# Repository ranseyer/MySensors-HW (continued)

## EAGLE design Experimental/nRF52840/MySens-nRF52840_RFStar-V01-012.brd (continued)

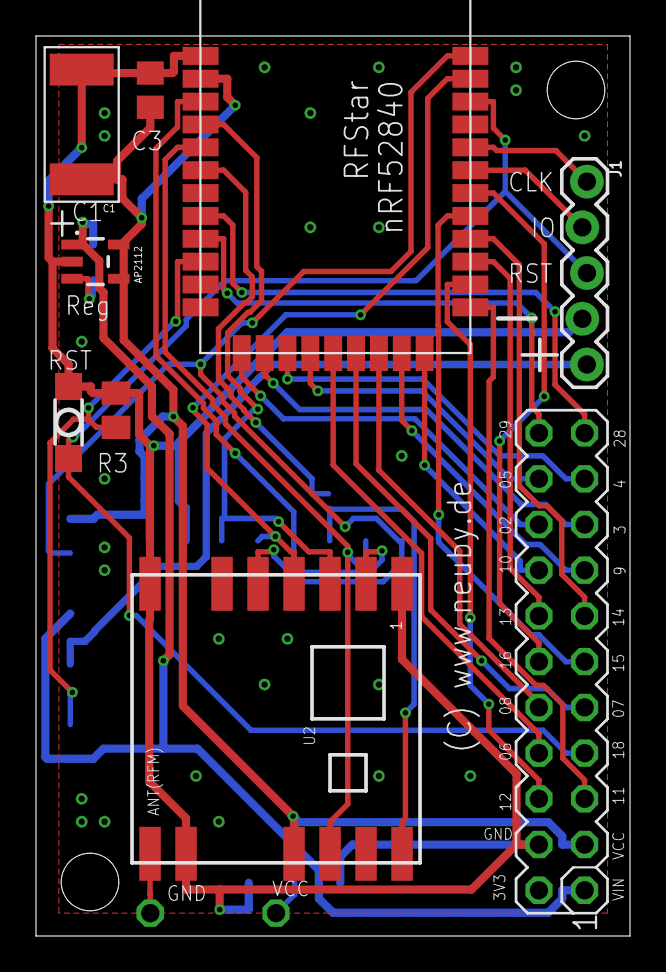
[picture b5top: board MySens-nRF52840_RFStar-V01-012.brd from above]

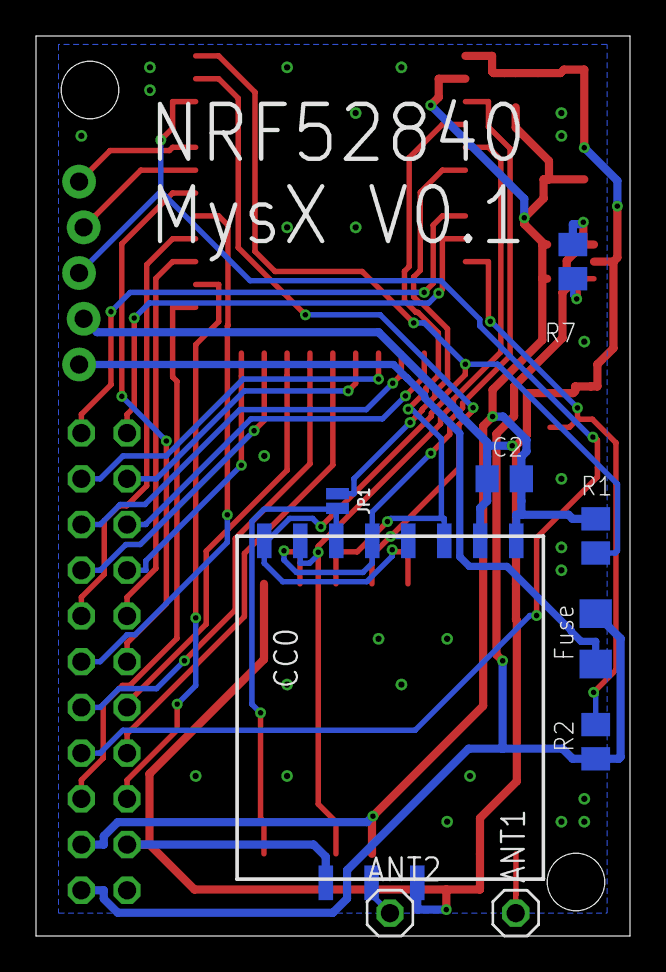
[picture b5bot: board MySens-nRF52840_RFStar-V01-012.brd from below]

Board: 2 copper layers, 33.0 x 50.0 mm, 18 parts (9 on the bottom side), 35 nets.

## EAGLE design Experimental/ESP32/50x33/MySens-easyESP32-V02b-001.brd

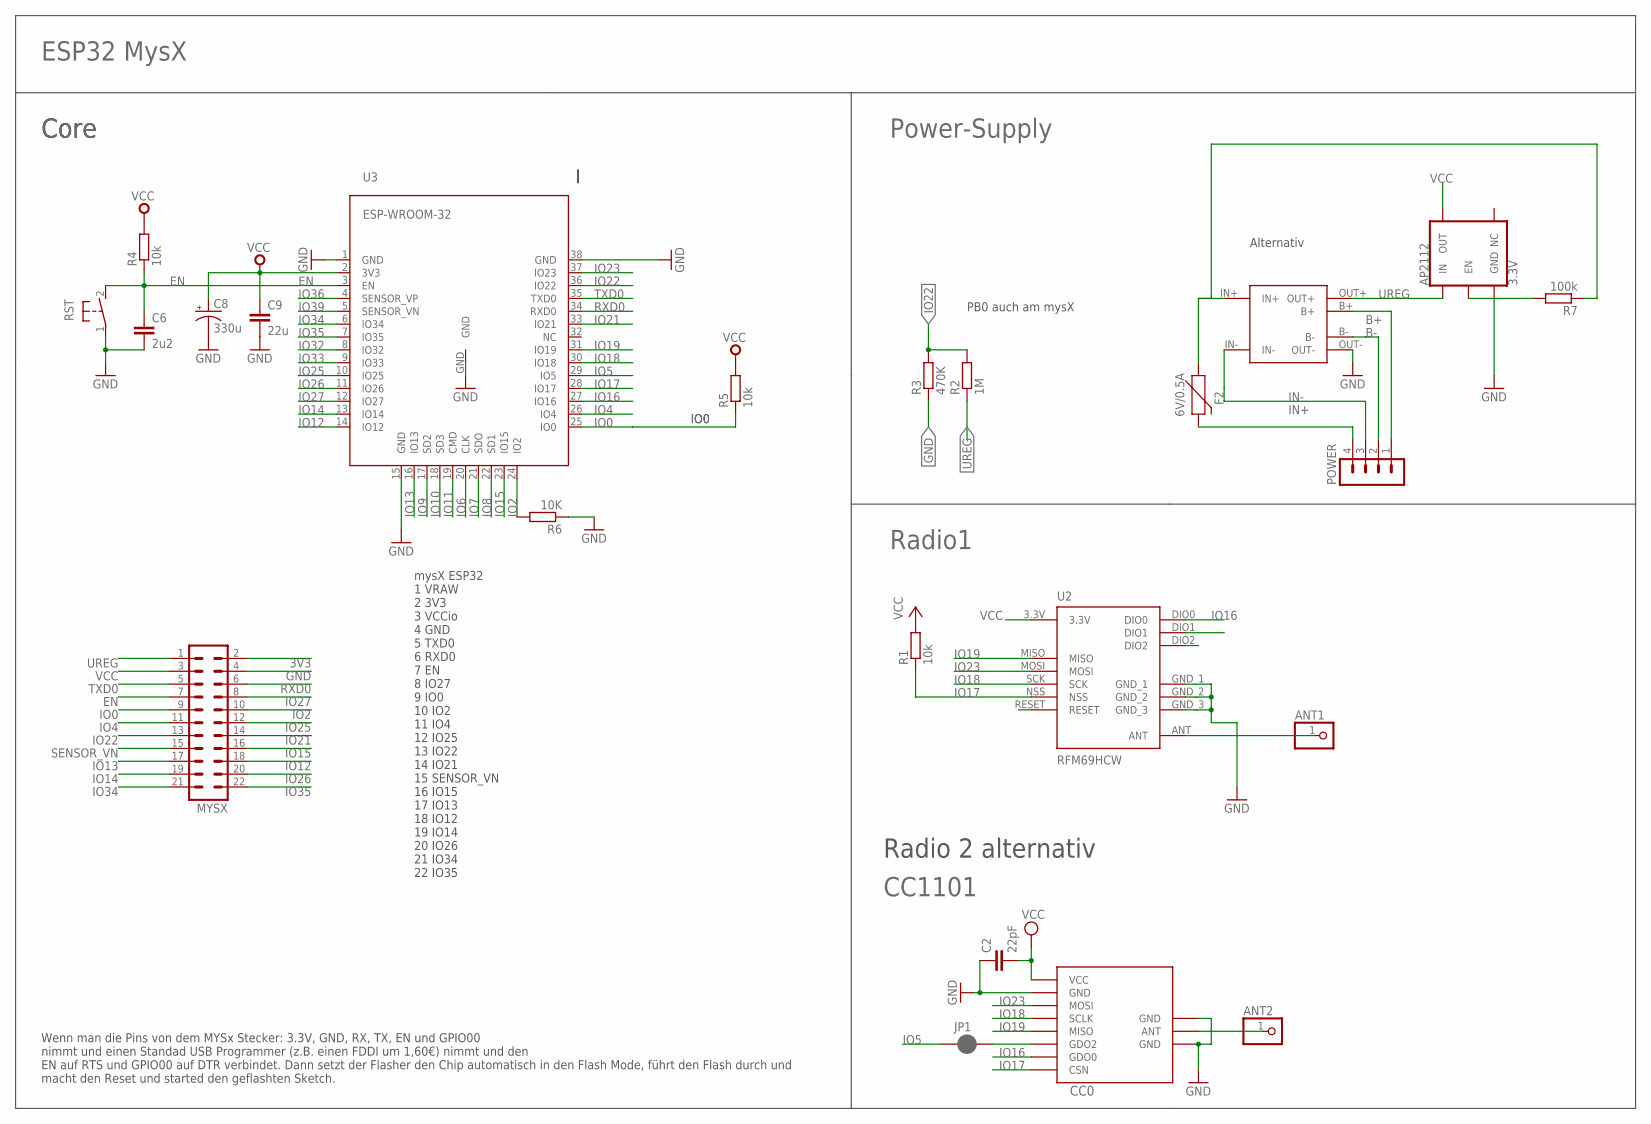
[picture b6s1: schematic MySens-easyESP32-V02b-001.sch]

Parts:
ANT1, ANT2: PINHD-1X1; 1X01
AP2112: 3.3V; SOT23-5
C2: 22pF; C0805
C6: 2u2; C0805
C8: 330u; VISHAY_C
C9: 22u; C0805
CC0: CC1101; CC1101_MODULE1_SMD
F2: 6V/0.5A; 1206
JP1: JUMPER-SMT_2_NC_PASTE_NO-SILK; SMT-JUMPER_2_NC_PASTE_NO-SILK
MYSX: MA11-2
POWER: MA04-1
R1, R4: 10k; M0805
R2: 1M; M0805
R3: 470K; M0805
R5: 10k; R0603
R6: 10K; M0805
R7: 100k; M0805
RST: DTSM-3
TP4056: TP4056-MODULE; TP4056-LITHIUM-PROTECTED-MODULE
U2: RFM69HCW; RFM69HCW-XXXS2
U3: ESP-WROOM-32

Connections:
3V3: MYSX.2
ANT0: ANT2.1, CC0.ANT
ANT1: ANT1.1, U2.ANT
B+: POWER.1, TP4056.B+
B-: POWER.2, TP4056.B-
EN: C6.1, MYSX.7, R4.1, RST.2, U3.3 (EN)
GND: AP2112.2 (GND), C2.1, C6.2, C8.-, C9.2, CC0.GND@0 (GND), CC0.GND@1 (GND), CC0.GND@2 (GND), MYSX.4, R3.1, R6.1, RST.1, TP4056.OUT-, U2.GND_1, U2.GND_2, U2.GND_3, U3.1 (GND), U3.15 (GND), U3.38 (GND), U3.GND
IN+: F2.2, POWER.4
IN++: F2.1, R7.1, TP4056.IN+
IN-: POWER.3, TP4056.IN-
IO0: MYSX.9, R5.1, U3.25 (IO0)
IO2: MYSX.10, R6.2, U3.24 (IO2)
IO4: MYSX.11, U3.26 (IO4)
IO5: JP1.1, U3.29 (IO5)
IO6: U3.20 (CLK)
IO7: U3.21 (SDO)
IO8: U3.22 (SD1)
IO9: U3.17 (SD2)
IO10: U3.18 (SD3)
IO11: U3.19 (CMD)
IO12: MYSX.18, U3.14 (IO12)
IO13: MYSX.17, U3.16 (IO13)
IO14: MYSX.19, U3.13 (IO14)
IO15: MYSX.16, U3.23 (IO15)
IO16: CC0.GDO0, U2.DIO0, U3.27 (IO16)
IO17: CC0.CSN, R1.1, U2.NSS, U3.28 (IO17)
IO18: CC0.SCLK, U2.SCK, U3.30 (IO18)
IO19: CC0.MISO, U2.MISO, U3.31 (IO19)
IO21: MYSX.14, U3.33 (IO21)
IO22: MYSX.13, R2.2, R3.2, U3.36 (IO22)
IO23: CC0.MOSI, U2.MOSI, U3.37 (IO23)
IO25: MYSX.12, U3.10 (IO25)
IO26: MYSX.20, U3.11 (IO26)
IO27: MYSX.8, U3.12 (IO27)
IO32: U3.8 (IO32)
IO33: U3.9 (IO33)
IO34: MYSX.21, U3.6 (IO34)
IO35: MYSX.22, U3.7 (IO35)
IO36: U3.4 (SENSOR_VP)
IO39: U3.5 (SENSOR_VN)
MAYBE_IO5: CC0.GDO2, JP1.2
unnamed: AP2112.3 (EN), R7.2
RXD0: MYSX.6, U3.34 (RXD0)
SENSOR_VN: MYSX.15
TXD0: MYSX.5, U3.35 (TXD0)
UREG: AP2112.1 (IN), MYSX.1, R2.1, TP4056.OUT+
VCC: AP2112.5 (OUT), C2.2, C8.+, C9.1, CC0.VCC, MYSX.3, R1.2, R4.2, R5.2, U2.3.3V, U3.2 (3V3)

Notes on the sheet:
mysX ESP32 1 VRAW 2 3V3 3 VCCio 4 GND 5 TXD0 6 RXD0 7 EN 8 IO27 9 IO0 10 IO2 11 IO4 12 IO25 13 IO22 14 IO21 15 SENSOR_VN 16 IO15 17 IO13 18 IO12 19 IO14 20 IO26 21 IO34 22 IO35
PB0 auch am mysX
Radio1
ESP32 MysX
Radio 2 alternativ
CC1101
Wenn man die Pins von dem MYSx Stecker: 3.3V, GND, RX, TX, EN und GPIO00 nimmt und einen Standad USB Programmer (z.B. einen FDDI um 1,60€) nimmt und den EN auf RTS und GPIO00 auf DTR verbindet. Dann setzt der Flasher den Chip automatisch in den Flash Mode, führt den Flash durch und macht den Reset 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
Alternativ
Core
Power-Supply

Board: 2 copper layers, 23 parts (11 on the bottom side), 35 nets, no tracks yet.

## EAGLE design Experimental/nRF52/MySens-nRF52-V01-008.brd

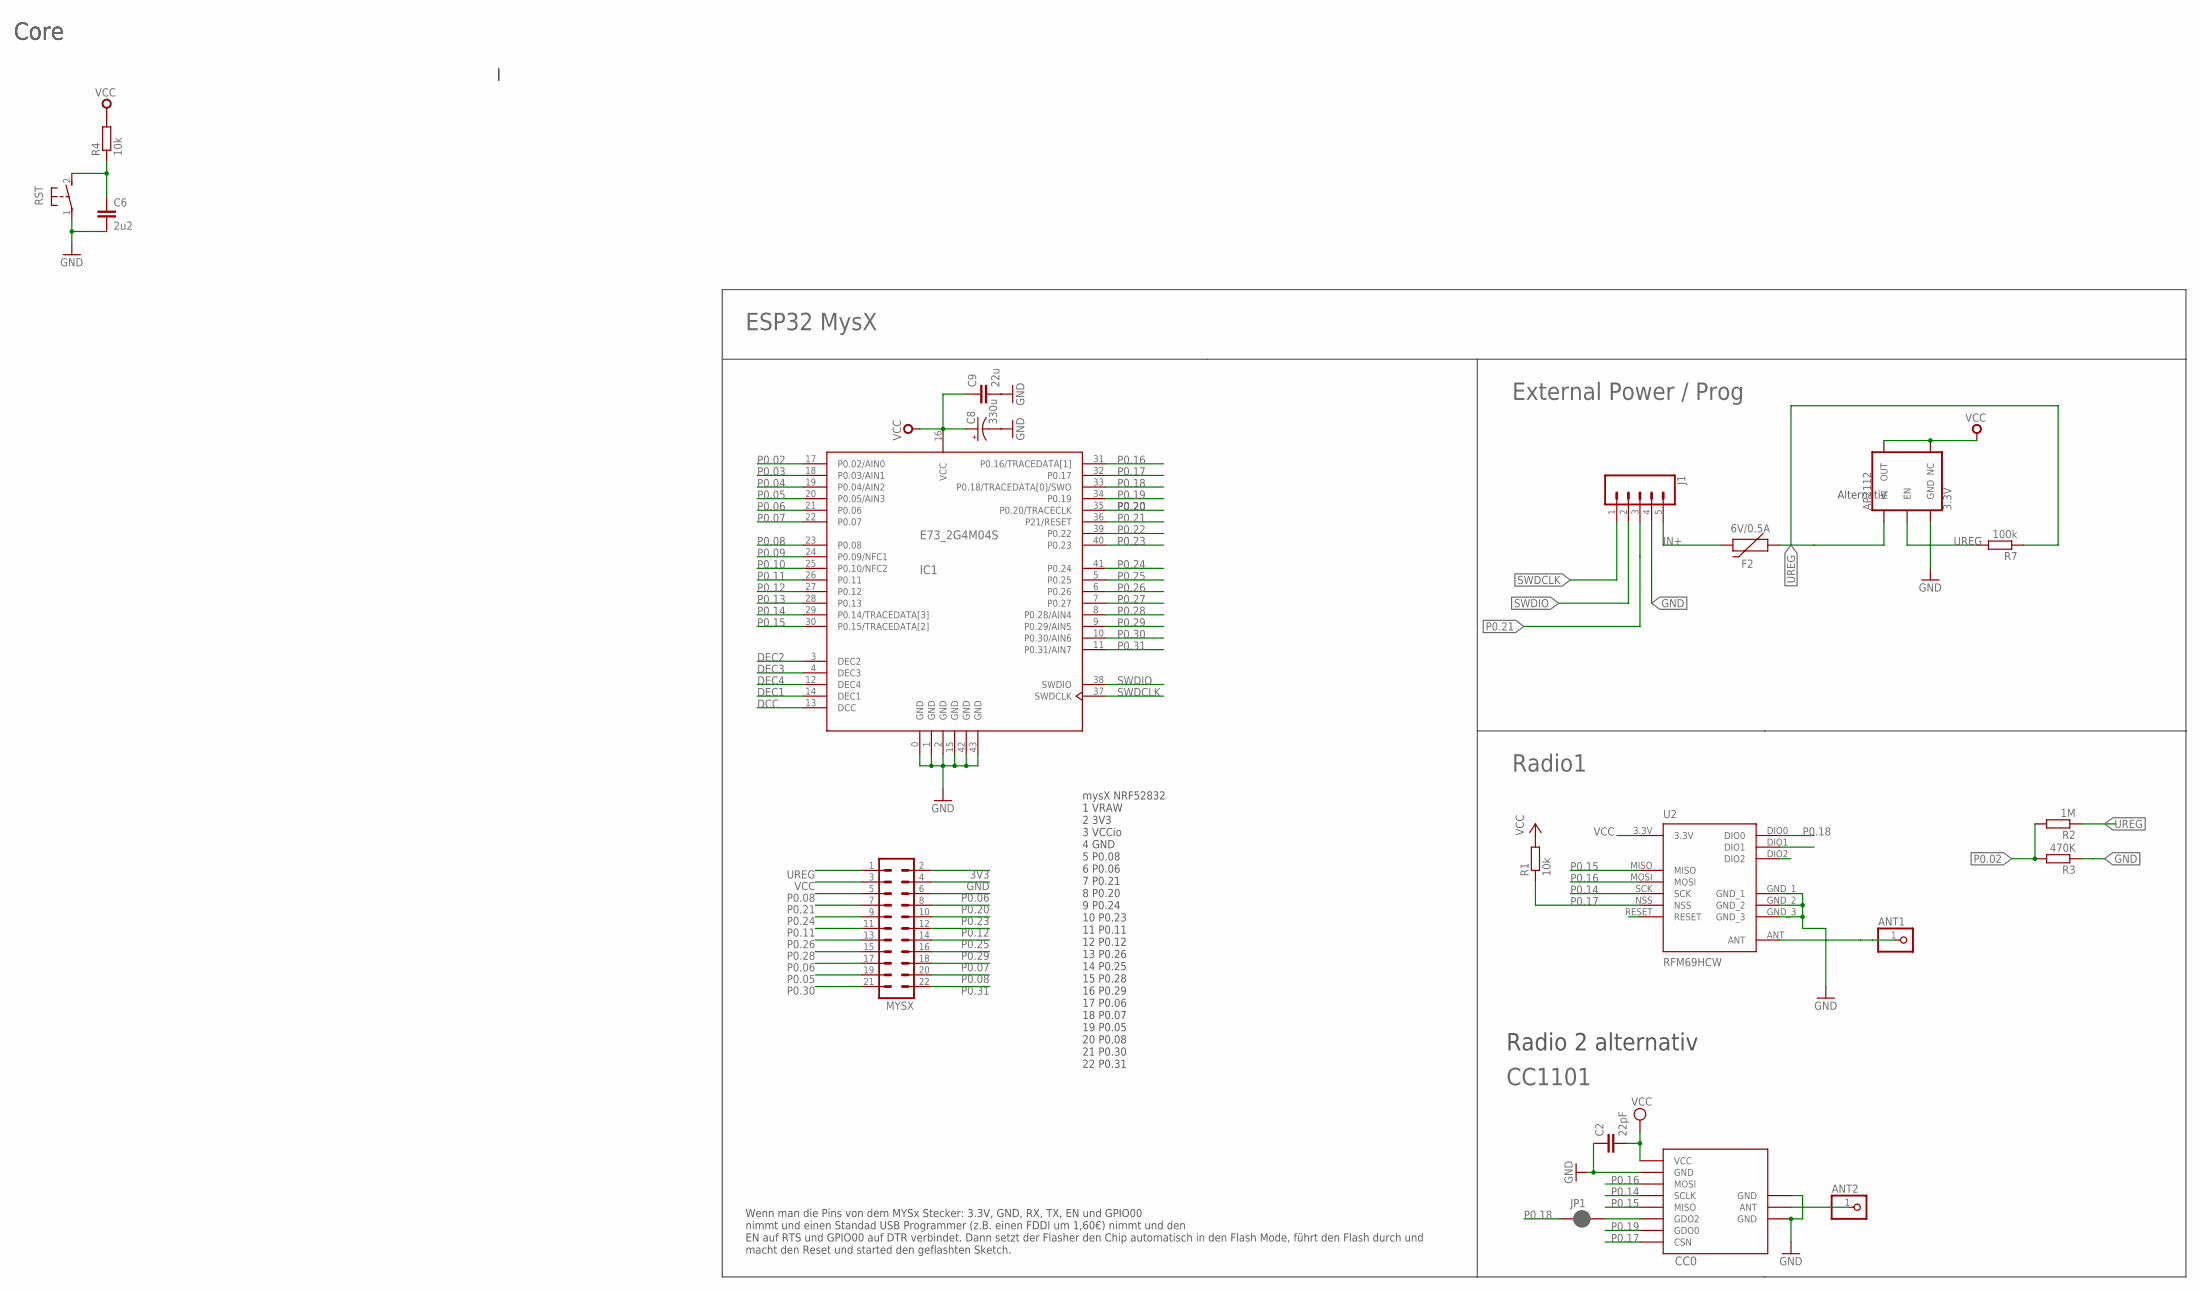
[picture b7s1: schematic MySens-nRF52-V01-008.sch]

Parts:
ANT1, ANT2: PINHD-1X1; 1X01
AP2112: 3.3V; SOT23-5
C2: 22pF; C0805
C6: 2u2; C0805
C8: 330u; VISHAY_C
C9: 22u; C0805
CC0: CC1101; CC1101_MODULE1_SMD
F2: 6V/0.5A; 1206
IC1: E73_2G4M04S
J1: CONN_05LOCK; 1X05_LOCK
JP1: JUMPER-SMT_2_NC_PASTE_NO-SILK; SMT-JUMPER_2_NC_PASTE_NO-SILK
MYSX: MA11-2
R1, R4: 10k; M0805
R2: 1M; M0805
R3: 470K; M0805
R7: 100k; M0805
RST: DTSM-3
U2: RFM69HCW; RFM69HCW-XXXS2

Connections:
3V3: MYSX.2
ANT0: ANT2.1, CC0.ANT
ANT1: ANT1.1, U2.ANT
DCC: IC1.13 (DCC)
DEC1: IC1.14 (DEC1)
DEC2: IC1.3 (DEC2)
DEC3: IC1.4 (DEC3)
DEC4: IC1.12 (DEC4)
GND: AP2112.2 (GND), C2.1, C6.2, C8.-, C9.2, CC0.GND@0 (GND), CC0.GND@1 (GND), CC0.GND@2 (GND), IC1.0 (GND), IC1.1 (GND), IC1.2 (GND), IC1.15 (GND), IC1.42 (GND), IC1.43 (GND), J1.4, MYSX.4, R3.1, RST.1, U2.GND_1, U2.GND_2, U2.GND_3
IN+: F2.2, J1.5
MAYBE_IO5: CC0.GDO2, JP1.2
unnamed: AP2112.3 (EN), R7.2
unnamed: C6.1, R4.1, RST.2
P0.02: IC1.17 (P0.02/AIN0), R2.2, R3.2
P0.03: IC1.18 (P0.03/AIN1)
P0.04: IC1.19 (P0.04/AIN2)
P0.05: IC1.20 (P0.05/AIN3), MYSX.19
P0.06: IC1.21 (P0.06), MYSX.6, MYSX.17
P0.07: IC1.22 (P0.07), MYSX.18
P0.08: IC1.23 (P0.08), MYSX.5, MYSX.20
P0.09: IC1.24 (P0.09/NFC1)
P0.10: IC1.25 (P0.10/NFC2)
P0.11: IC1.26 (P0.11), MYSX.11
P0.12: IC1.27 (P0.12), MYSX.12
P0.13: IC1.28 (P0.13)
P0.14: CC0.SCLK, IC1.29 (P0.14/TRACEDATA[3]), U2.SCK
P0.15: CC0.MISO, IC1.30 (P0.15/TRACEDATA[2]), U2.MISO
P0.16: CC0.MOSI, IC1.31 (P0.16/TRACEDATA[1]), U2.MOSI
P0.17: CC0.CSN, IC1.32 (P0.17), R1.1, U2.NSS
P0.18: IC1.33 (P0.18/TRACEDATA[0]/SWO), JP1.1, U2.DIO0
P0.19: CC0.GDO0, IC1.34 (P0.19)
P0.20: IC1.35 (P0.20/TRACECLK), MYSX.8
P0.21: IC1.36 (P21/RESET), J1.3, MYSX.7
P0.22: IC1.39 (P0.22)
P0.23: IC1.40 (P0.23), MYSX.10
P0.24: IC1.41 (P0.24), MYSX.9
P0.25: IC1.5 (P0.25), MYSX.14
P0.26: IC1.6 (P0.26), MYSX.13
P0.27: IC1.7 (P0.27)
P0.28: IC1.8 (P0.28/AIN4), MYSX.15
P0.29: IC1.9 (P0.29/AIN5), MYSX.16
P0.30: IC1.10 (P0.30/AIN6), MYSX.21
P0.31: IC1.11 (P0.31/AIN7), MYSX.22
SWDCLK: IC1.37 (SWDCLK), J1.1
SWDIO: IC1.38 (SWDIO), J1.2
UREG: AP2112.1 (IN), F2.1, MYSX.1, R2.1, R7.1
VCC: AP2112.4 (NC), AP2112.5 (OUT), C2.2, C8.+, C9.1, CC0.VCC, IC1.16 (VCC), MYSX.3, R1.2, R4.2, U2.3.3V

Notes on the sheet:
mysX NRF52832 1 VRAW 2 3V3 3 VCCio 4 GND 5 P0.08 6 P0.06 7 P0.21 8 P0.20 9 P0.24 10 P0.23 11 P0.11 12 P0.12 13 P0.26 14 P0.25 15 P0.28 16 P0.29 17 P0.06 18 P0.07 19 P0.05 20 P0.08 21 P0.30 22 P0.31
Radio1
ESP32 MysX
Radio 2 alternativ
CC1101
Wenn man die Pins von dem MYSx Stecker: 3.3V, GND, RX, TX, EN und GPIO00 nimmt und einen Standad USB Programmer (z.B. einen FDDI um 1,60€) nimmt und den EN auf RTS und GPIO00 auf DTR verbindet. Dann setzt der Flasher den Chip automatisch in den Flash Mode, führt den Flash durch und macht den Reset 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
Alternativ
Core
External Power / Prog

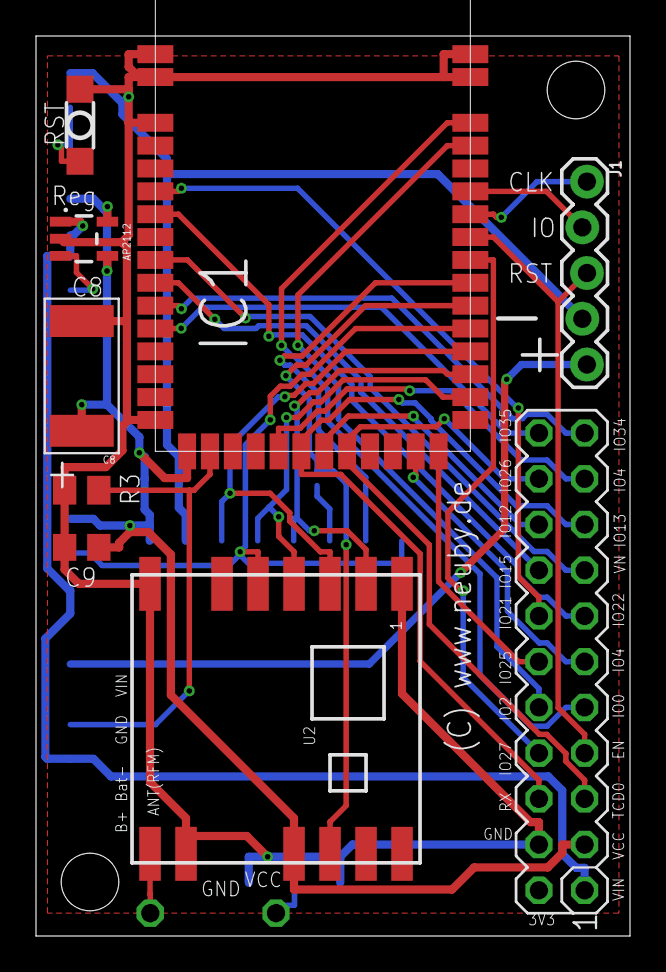
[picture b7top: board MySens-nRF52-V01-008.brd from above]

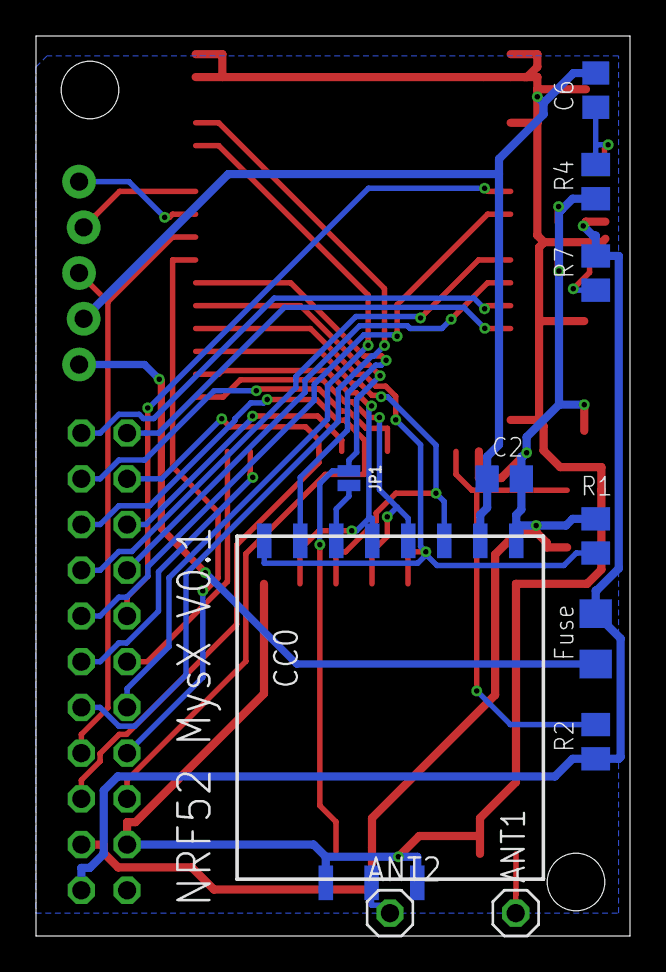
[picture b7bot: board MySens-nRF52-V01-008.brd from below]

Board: 2 copper layers, 33.0 x 50.0 mm, 20 parts (11 on the bottom side), 34 nets.

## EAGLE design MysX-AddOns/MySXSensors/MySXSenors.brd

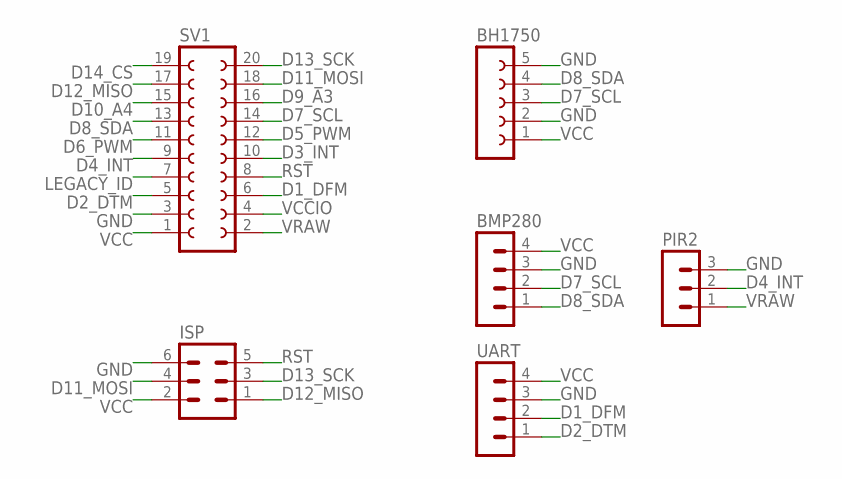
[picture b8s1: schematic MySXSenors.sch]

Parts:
BH1750: FE05-1
BMP280: MA04-1
ISP: MA03-2
PIR2: MA03-1
SV1: FE10-2
UART: MA04-1

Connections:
D1_DFM: SV1.6, UART.2
D2_DTM: SV1.5, UART.1
D3_INT: SV1.10
D4_INT: PIR2.2, SV1.9
D5_PWM: SV1.12
D6_PWM: SV1.11
D7_SCL: BH1750.3, BMP280.2, SV1.14
D8_SDA: BH1750.4, BMP280.1, SV1.13
D9_A3: SV1.16
D10_A4: SV1.15
D11_MOSI: ISP.4, SV1.18
D12_MISO: ISP.1, SV1.17
D13_SCK: ISP.3, SV1.20
D14_CS: SV1.19
GND: BH1750.2, BH1750.5, BMP280.3, ISP.6, PIR2.3, SV1.3, UART.3
LEGACY_ID: SV1.7
RST: ISP.5, SV1.8
VCC: BH1750.1, BMP280.4, ISP.2, SV1.1, UART.4
VCCIO: SV1.4
VRAW: PIR2.1, SV1.2

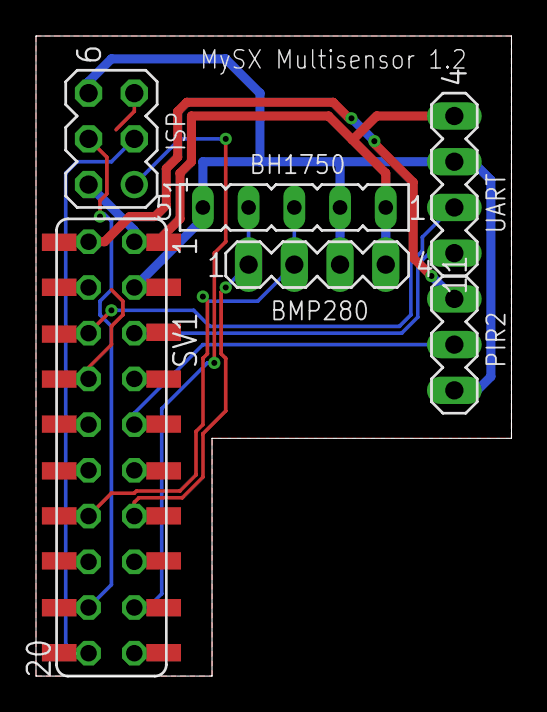
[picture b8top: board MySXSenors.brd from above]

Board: 2 copper layers, 26.4 x 35.6 mm, 6 parts (0 on the bottom side), 12 nets.

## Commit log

2017-10-31 initial
2017-12-15 Updates for GW + Mini
2017-12-20 V2 Reworked
2017-12-22 Update RFM95
2017-12-22 Docu
2017-12-25 RS485-Nano 1st draft
2017-12-26 RS485 Nano with MySX2.6
2017-12-26 1117
2017-12-27 RS485 New SubBoard
2017-12-29 Nano RS485
2017-12-30 RJ45 for Gateway
2017-12-30 Overview Photos
2017-12-30 ProMicro GW 1st Version
2017-12-31 RS485 Pro Mico ready for test
2017-12-31 Maple Test
2017-12-31 Maple V01
2018-01-01 Pro-Micro Docs
2018-01-16 PCBs with RJ45 Sockets
2018-01-16 SAMD Board
2018-02-05 Cleanup
2018-02-09 Maple RS485
2018-02-19 SAMD 1st try (NOK!) +NanoRS485 Update
2018-03-25 LoRa 1
2018-03-29 Mini RS485
2018-03-30 BluePill, MiniRS485 Sensor+Gateway
2018-04-28 STM32 Maple => Bluepill
2018-05-01 STM32 and other Updates
2018-05-01 stm32 update
2018-06-08 Backlink to CADLAB.io has been added.
2018-06-13 CAN Sensor / Gateway
2018-06-14 Rework CAN
2018-06-14 Schematic
2018-06-18 CAN/RS485 Board
2018-06-18 ESP32
2018-06-30 ESP32 and others
2018-06-30 little cleanup
2018-06-30 ESP32 SMD
2018-07-03 ESP32 AddOn
2018-07-07 STM32
2018-08-05 RFM-Mini GW
2018-08-07 AddOns
2018-11-04 nRF52
2018-12-05 nRF +RouterTest
2018-12-27 AddOn V02
2019-02-15 images
2019-02-22 Display fix
2019-03-04 Mini RFM-V03
2019-05-01 RS485 Boards
